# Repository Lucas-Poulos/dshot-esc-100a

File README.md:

# dshot-esc-100a

A 12 V, 100 A three-phase **all-N-channel** motor driver for a high-power
drone motor, controllable over **DShot150/300/600/1200**.

| | |
|---|---|
| Battery | 3S LiPo, 9.0–12.6 V (operating range 6–16 V) |
| Continuous | **100 A** (~1.2 kW) |
| Burst | **150 A** for 10 s |
| Bridge | 6 switch positions × **2 paralleled N-channel MOSFETs = 12 total** |
| Gate driver | **DRV8323R** (RS or RH — one footprint, both variants) |
| Controller | **STM32G071CBT6** running **AM32** |
| Control | DShot150/300/600/1200, bidirectional, + ESC telemetry |
| Efficiency | ~98.5 % at 100 A (≈19 W dissipated) |

**Status: schematic complete and ERC-clean (160 components). PCB floorplanned
and DRC-clean — 80 × 68 mm, 4 layers, 2 oz outer. Routing not started.**

---

## Why all N-channel, and how the high side is driven

A P-channel high-side switch is the easy way to build a bridge and the
wrong way here — P-channel parts with usable R_DS(on) at 100 A don't exist
in a sane package. Both rails are N-channel, so the high-side gate has to
be driven above the battery rail.

The DRV8323R does that with an on-chip **charge pump**, not a bootstrap
capacitor. A bootstrap cap must be refreshed by pulling the phase node
low, which caps duty cycle below 100 %. A charge pump holds the gate up
indefinitely, so the high-side FET stays fully enhanced at **100 % duty** —
exactly the regime "drive it hard" lives in.

## Shoot-through: four independent layers

Shoot-through at 12 V into 2 × 0.43 mΩ is roughly **14 kA**, limited only
by parasitics. It destroys the bridge in microseconds and no fuse is fast
enough. So it's prevented four times over, and no single layer is trusted:

| Layer | Mechanism | Independent of |
|---|---|---|
| 1 | TIM1 hardware dead-time generator, **625 ns** | firmware timing bugs |
| 2 | DRV8323R cross-conduction lockout + 100 ns | the MCU entirely |
| 3 | 6 × SN74LVC1G97 combinational interlock | MCU *and* driver |
| 4 | Gate-source pulldowns + per-FET series gate resistors | everything active |
| 0 | `nFAULT` → `TIM1_BKIN` kills all 6 outputs in hardware | firmware latency |

The dead-time budget works out **negative** under nominal conditions —
because sink current is set 3.5× source current, the outgoing FET is
already off before the incoming one conducts. The 625 ns is therefore pure
margin against V_th spread, tempco, and gate ringing. Full derivation from
the FET's measured gate charge: **[`docs/shoot-through.md`](docs/shoot-through.md)**.

## Documentation

| Document | What's in it |
|---|---|
| [`docs/architecture.md`](docs/architecture.md) | topology, block diagram, sheet map, design decisions |
| [`docs/shoot-through.md`](docs/shoot-through.md) | the four layers, dead-time budget, DTG encoding |
| [`docs/power-budget.md`](docs/power-budget.md) | conduction/switching/shunt losses, thermals, why 2 FETs not 3 |
| [`docs/pinout.md`](docs/pinout.md) | full 48-pin MCU map + AM32 hardware group |
| [`docs/gate-driver-config.md`](docs/gate-driver-config.md) | RH vs RS dual build, every register value derived |
| [`docs/layout.md`](docs/layout.md) | stackup, floorplan, and the routing rules — **read before routing** |
| [`docs/references.md`](docs/references.md) | every datasheet and firmware source used |
| [`firmware/README.md`](firmware/README.md) | AM32 target, SPI init, flashing, **bring-up order** |
| [`manufacturing/BOM.md`](manufacturing/BOM.md) | generated from the netlist, real LCSC numbers |
| [`manufacturing/dshot-esc-100a/ISSUES.md`](manufacturing/dshot-esc-100a/ISSUES.md) | 12 open items — read before fabricating |

## Repository layout

```
design/          GENERATED KiCad 10 project — schematic never saved from the GUI
  01_power_in  02_gate_driver  03_power_stage
  04_mcu       05_sense        06_protection
  lib/         DRV8323R + STM32G071CBTx symbols
scripts/        the source of truth for everything in design/
  gen_custom_symbols.py  gen_project.py  wire_sheets.py
  gen_footprints.py      gen_pcb.py      verify_project.py
  gen_bom.py             calc_*.py
  kicad_sch.py           kicad_symlib.py
docs/           design documentation
firmware/       AM32 target + DRV8323RS SPI driver
datasheets/     22 PDFs, synced from LCSC
manufacturing/  BOM, schematic PDF, issue tracker
```

## Reproducing the design

```bash
pgrep -fil kicad                            # must be empty first
python3 scripts/gen_custom_symbols.py       # symbol library
python3 scripts/gen_project.py --verify     # refuses to write if broken
python3 scripts/gen_project.py              # sheets + placement + wiring
python3 scripts/gen_bom.py
python3 scripts/verify_project.py           # the real gate
```

The calculations behind the docs are runnable, not asserted:

```bash
python3 scripts/calc_deadtime.py    # DTG table + dead-time budget
python3 scripts/calc_power.py       # loss and thermal budget
```

## Before you build one

Read [`ISSUES.md`](manufacturing/dshot-esc-100a/ISSUES.md). 11 open, 2
resolved. The ones that still matter most:

- **ESC-001** — the input ripple budget (~50 A RMS) isn't closed.
- **ESC-005** — the shunt needs a Kelvin sense tap in layout; at 0.25 mΩ
  a few mΩ of shared trace is a large error.
- **ESC-012** — 19 W is **not** passively coolable; this design assumes
  forced air.
- **ESC-007** — the buck feedback divider is unverified. Check it before
  first power-on or the MCU may sit outside its supply range.

And follow the bring-up order in `firmware/README.md`. Do not put a motor
on this board first.

## Licence

Hardware: CERN-OHL-S v2. Firmware snippets: MIT, matching AM32.

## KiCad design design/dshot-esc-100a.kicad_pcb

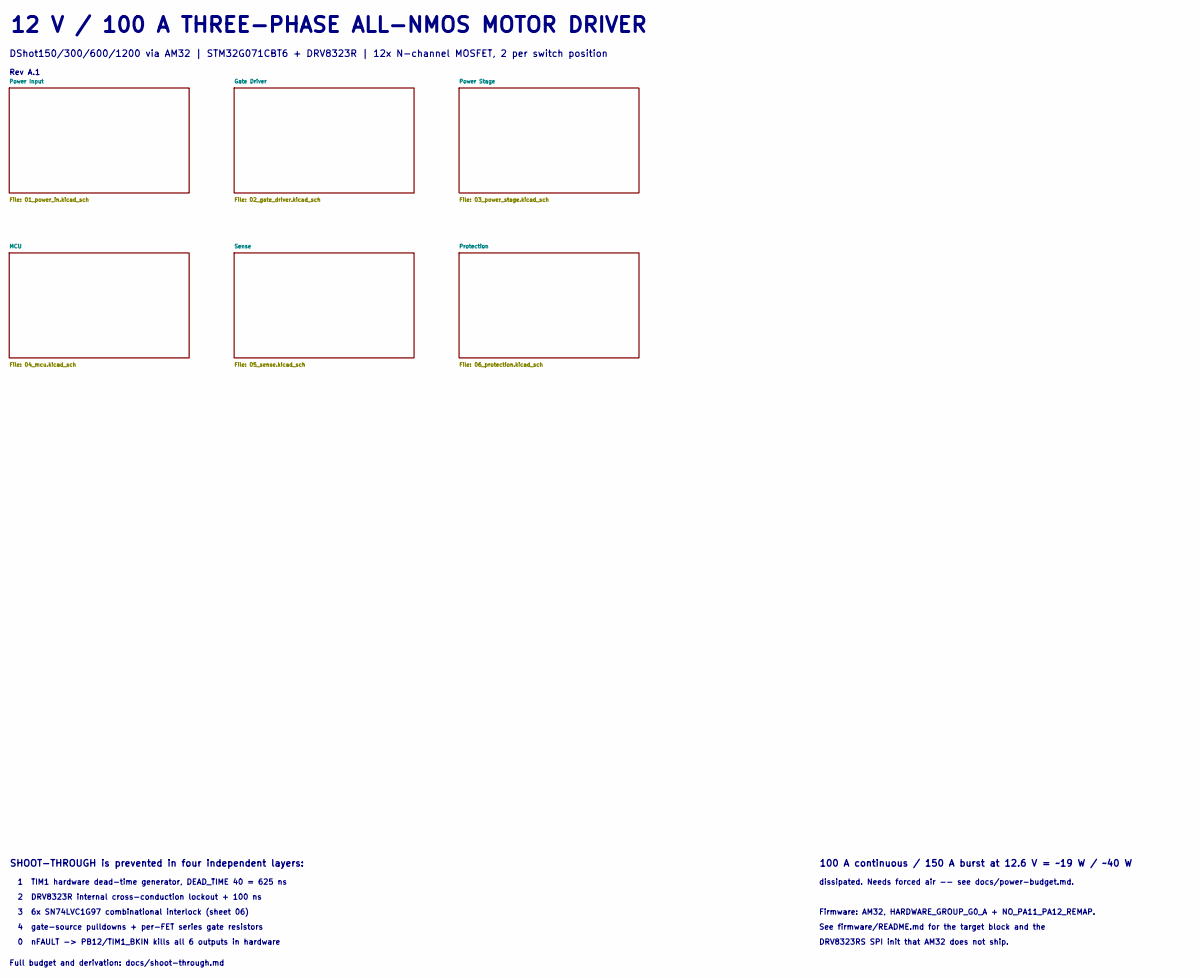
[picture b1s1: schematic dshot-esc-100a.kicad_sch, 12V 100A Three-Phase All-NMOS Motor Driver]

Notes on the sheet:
2 DRV8323R internal cross-conduction lockout + 100 ns
Full budget and derivation: docs/shoot-through.md
dissipated. Needs forced air -- see docs/power-budget.md.
12 V / 100 A THREE-PHASE ALL-NMOS MOTOR DRIVER
Rev A.1
See firmware/README.md for the target block and the
DRV8323RS SPI init that AM32 does not ship.
4 gate-source pulldowns + per-FET series gate resistors
SHOOT-THROUGH is prevented in four independent layers:
1 TIM1 hardware dead-time generator, DEAD_TIME 40 = 625 ns
Firmware: AM32, HARDWARE_GROUP_G0_A + NO_PA11_PA12_REMAP.
DShot150/300/600/1200 via AM32 | STM32G071CBT6 + DRV8323R | 12x N-channel MOSFET, 2 per switch position
0 nFAULT -> PB12/TIM1_BKIN kills all 6 outputs in hardware
3 6x SN74LVC1G97 combinational interlock (sheet 06)
100 A continuous / 150 A burst at 12.6 V = ~19 W / ~40 W

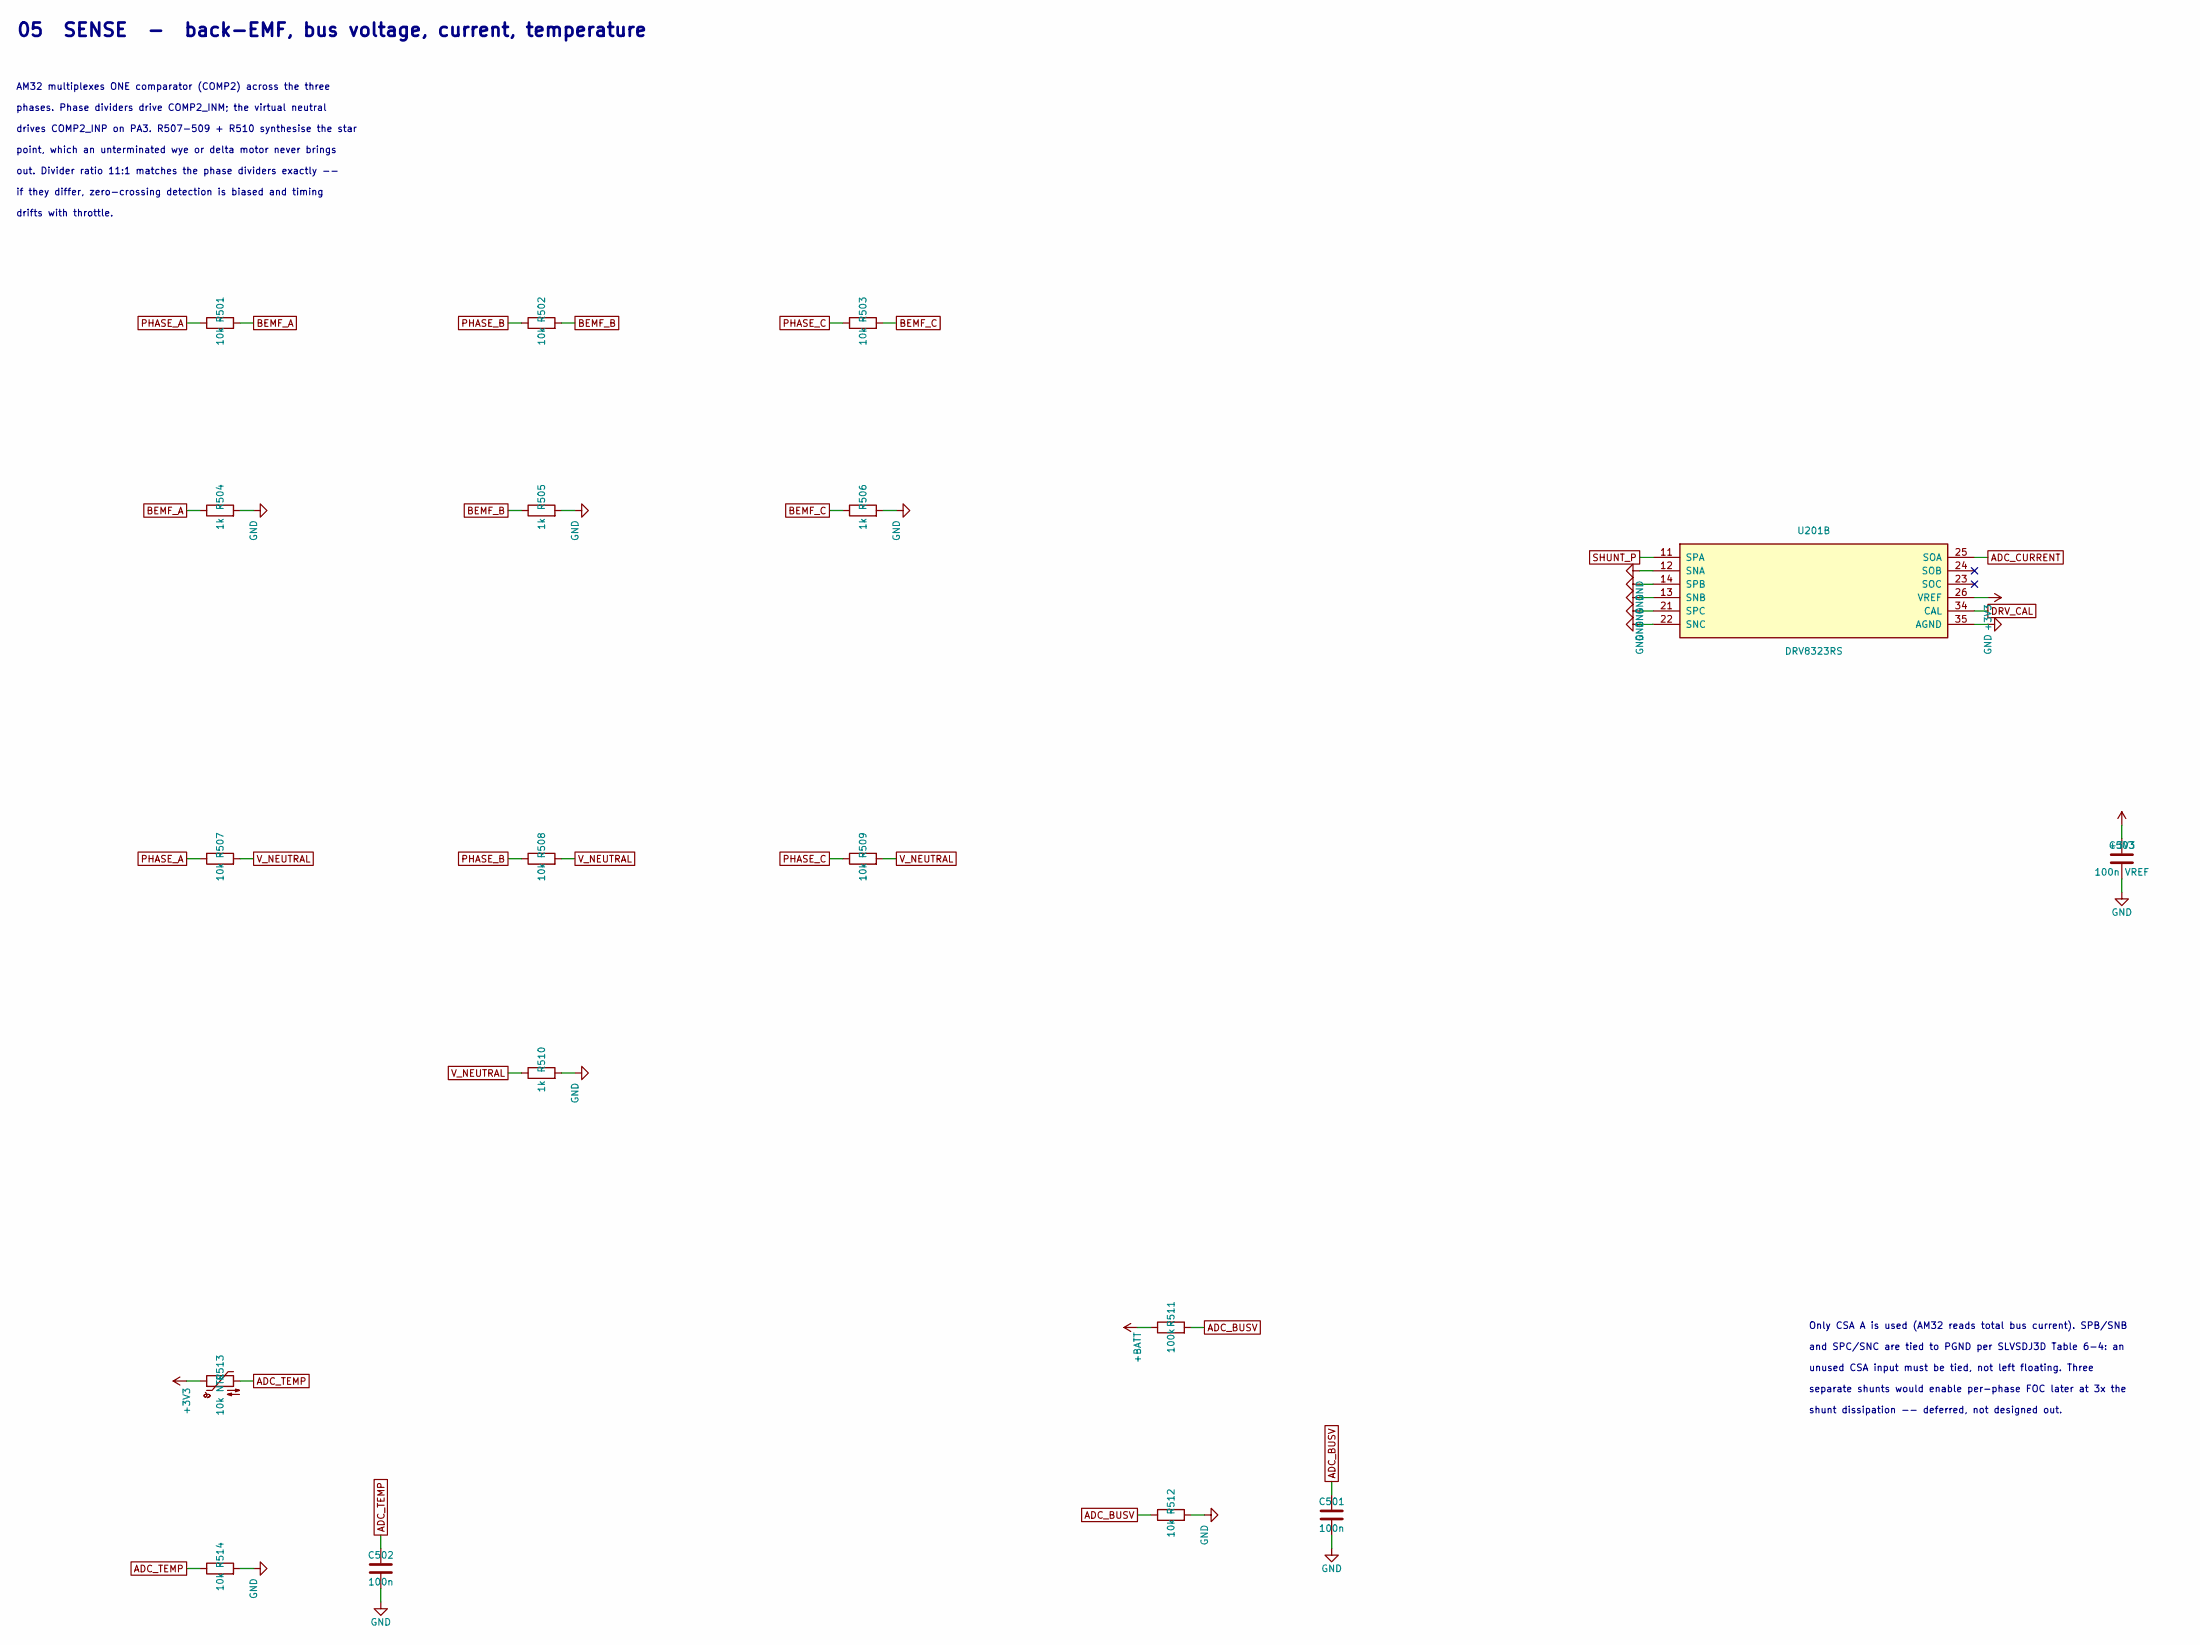
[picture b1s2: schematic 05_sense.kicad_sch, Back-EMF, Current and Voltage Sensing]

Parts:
C501, C502: 100n; C_0603_1608Metric; MPN CC0603KRX7R9BB104; LCSC C14663
C503: 100n VREF; C_0603_1608Metric; MPN CC0603KRX7R9BB104; LCSC C14663
R501, R502, R503, R507, R508, R509, R512, R514: 10k; R_0603_1608Metric; MPN FRC0603F1002TS; LCSC C2906982
R504, R505, R506, R510: 1k; R_0603_1608Metric; MPN FRC0603F1001TS; LCSC C2907002
R511: 100k; R_0603_1608Metric; MPN 0603WAF1003T5E; LCSC C25803
R513: 10k NTC; R_0603_1608Metric; MPN NCP18XH103F03RB; LCSC C13564
U201: DRV8323RS; Texas_RGZ0048A_VQFN-48-1EP_7x7mm_P0.5mm_EP5.15x5.15mm; MPN DRV8323RSRGZT; LCSC C2653553

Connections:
+3V3: C503.1, R513.1, U201.26 (VREF); also elsewhere on the board
+BATT: R511.1; also elsewhere on the board
ADC_BUSV: C501.1, R511.2, R512.1; also elsewhere on the board
ADC_CURRENT: U201.25 (SOA); also elsewhere on the board
ADC_TEMP: C502.1, R513.2, R514.1; also elsewhere on the board
BEMF_A: R501.2, R504.1; also elsewhere on the board
BEMF_B: R502.2, R505.1; also elsewhere on the board
BEMF_C: R503.2, R506.1; also elsewhere on the board
DRV_CAL: U201.34 (CAL); also elsewhere on the board
GND: C501.2, C502.2, C503.2, R504.2, R505.2, R506.2, R510.2, R512.2, R514.2, U201.12 (SNA), U201.13 (SNB), U201.14 (SPB), U201.21 (SPC), U201.22 (SNC), U201.35 (AGND); also elsewhere on the board
PHASE_A: R501.1, R507.1; also elsewhere on the board
PHASE_B: R502.1, R508.1; also elsewhere on the board
PHASE_C: R503.1, R509.1; also elsewhere on the board
SHUNT_P: U201.11 (SPA); also elsewhere on the board
V_NEUTRAL: R507.2, R508.2, R509.2, R510.1; also elsewhere on the board

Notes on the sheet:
point, which an unterminated wye or delta motor never brings
out. Divider ratio 11:1 matches the phase dividers exactly --
shunt dissipation -- deferred, not designed out.
05 SENSE - back-EMF, bus voltage, current, temperature
drives COMP2_INP on PA3. R507-509 + R510 synthesise the star
drifts with throttle.
unused CSA input must be tied, not left floating. Three
AM32 multiplexes ONE comparator (COMP2) across the three
phases. Phase dividers drive COMP2_INM; the virtual neutral
if they differ, zero-crossing detection is biased and timing
separate shunts would enable per-phase FOC later at 3x the
and SPC/SNC are tied to PGND per SLVSDJ3D Table 6-4: an
Only CSA A is used (AM32 reads total bus current). SPB/SNB

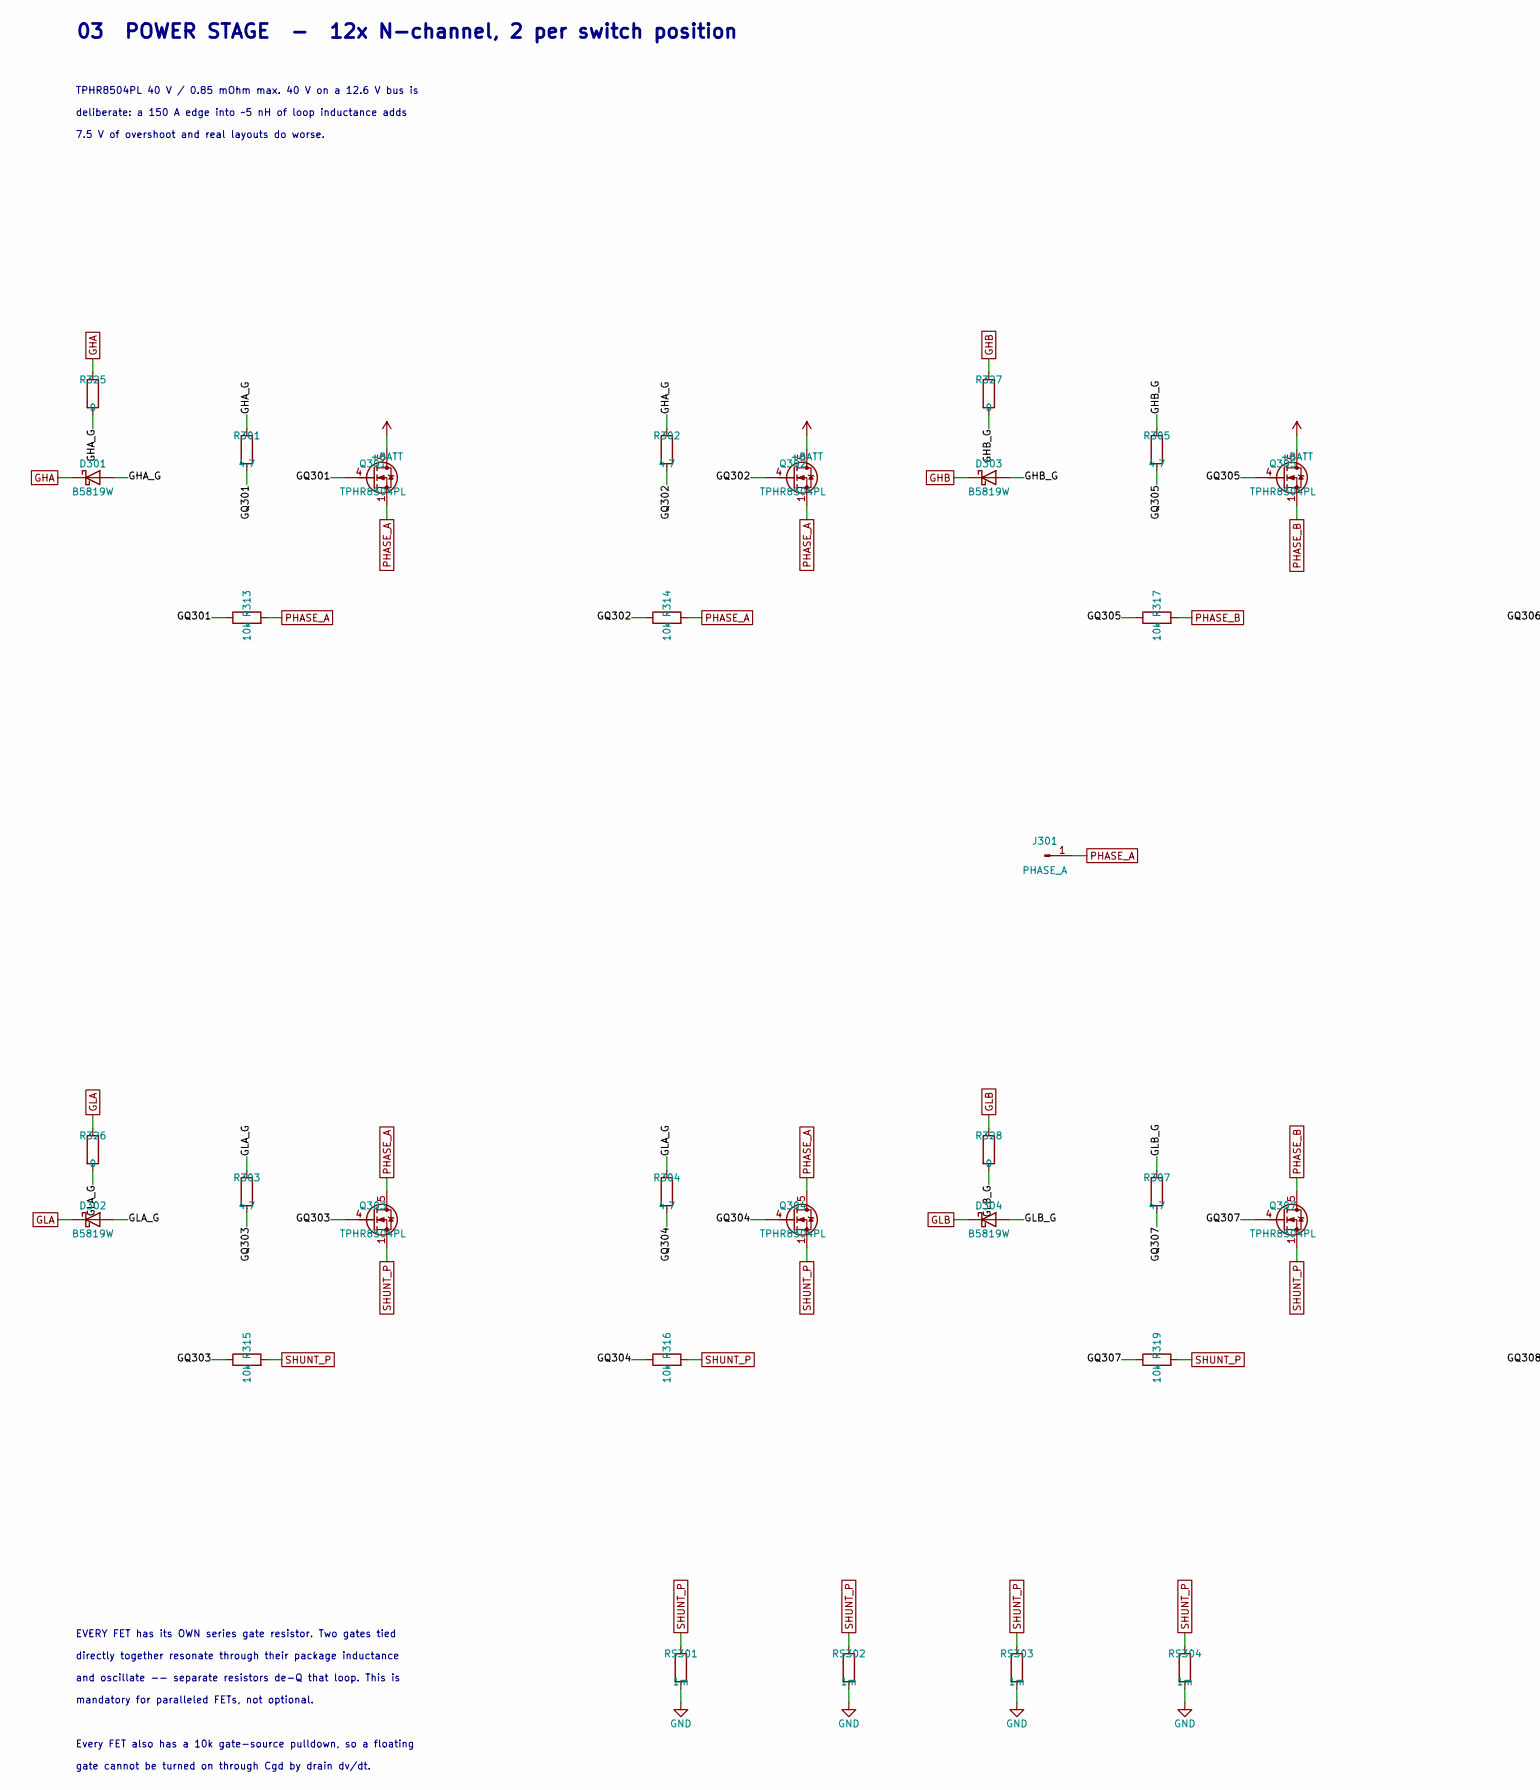
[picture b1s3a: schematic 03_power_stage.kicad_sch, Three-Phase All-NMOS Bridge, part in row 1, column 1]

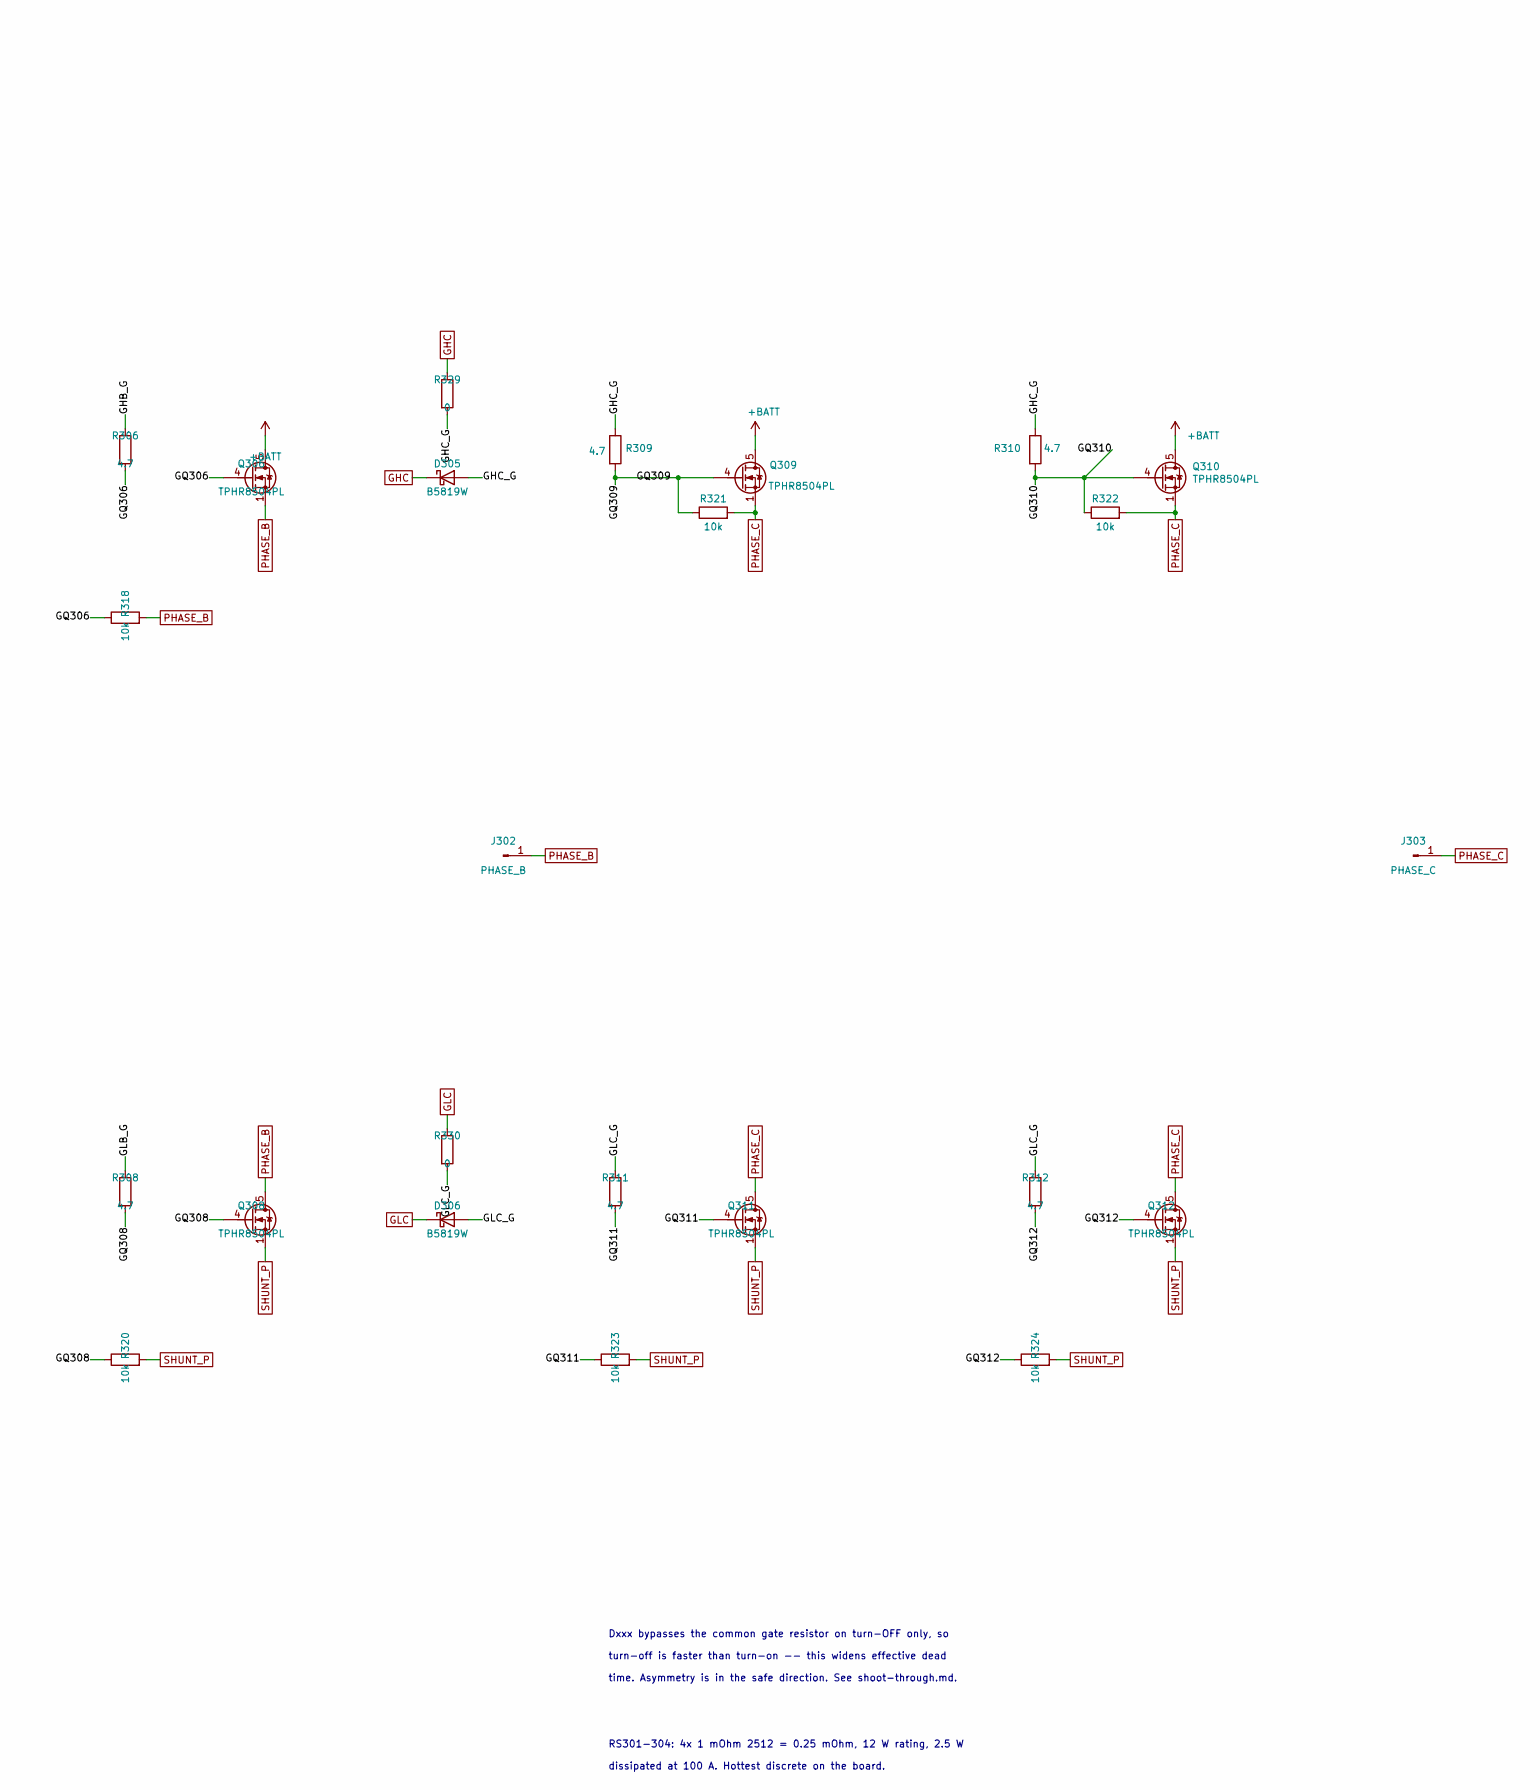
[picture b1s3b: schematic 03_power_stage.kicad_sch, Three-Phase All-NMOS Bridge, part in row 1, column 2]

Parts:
D301, D302, D303, D304, D305, D306: B5819W; D_SOD-123; MPN B5819W SL; LCSC C8598
J301: PHASE_A; HighCurrentTerminal_8AWG
J302: PHASE_B; HighCurrentTerminal_8AWG
J303: PHASE_C; HighCurrentTerminal_8AWG
Q301, Q302, Q303, Q304, Q305, Q306, Q307, Q308, Q309, Q310, Q311, Q312: TPHR8504PL; PQFN-8-EP_6x5mm_P1.27mm_Generic; MPN TPHR8504PL,L1Q(M; LCSC C5331611
R301, R302, R303, R304, R305, R306, R307, R308, R309, R310, R311, R312: 4.7; R_0805_2012Metric; MPN FRC0805F4R70TS; LCSC C2933459
R313, R314, R315, R316, R317, R318, R319, R320, R321, R322, R323, R324: 10k; R_0603_1608Metric; MPN FRC0603F1002TS; LCSC C2906982
R325, R326, R327, R328, R329, R330: 0; R_0603_1608Metric; MPN RCA030RLF; LCSC C22356631
RS301, RS302, RS303, RS304: 1m; R_2512_6332Metric; MPN HoJLR2512-3W-1mR-1%; LCSC C2903470

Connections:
+BATT: Q301.5 (D), Q302.5 (D), Q305.5 (D), Q306.5 (D), Q309.5 (D), Q310.5 (D); also elsewhere on the board
/Power Stage/GHA_G: D301.2 (A), R301.1, R302.1, R325.2
/Power Stage/GHB_G: D303.2 (A), R305.1, R306.1, R327.2
/Power Stage/GHC_G: D305.2 (A), R309.1, R310.1, R329.2
/Power Stage/GLA_G: D302.2 (A), R303.1, R304.1, R326.2
/Power Stage/GLB_G: D304.2 (A), R307.1, R308.1, R328.2
/Power Stage/GLC_G: D306.2 (A), R311.1, R312.1, R330.2
/Power Stage/GQ301: Q301.4 (G), R301.2, R313.1
/Power Stage/GQ302: Q302.4 (G), R302.2, R314.1
/Power Stage/GQ303: Q303.4 (G), R303.2, R315.1
/Power Stage/GQ304: Q304.4 (G), R304.2, R316.1
/Power Stage/GQ305: Q305.4 (G), R305.2, R317.1
/Power Stage/GQ306: Q306.4 (G), R306.2, R318.1
/Power Stage/GQ307: Q307.4 (G), R307.2, R319.1
/Power Stage/GQ308: Q308.4 (G), R308.2, R320.1
/Power Stage/GQ309: Q309.4 (G), R309.2, R321.1
/Power Stage/GQ310: Q310.4 (G), R310.2, R322.1
/Power Stage/GQ311: Q311.4 (G), R311.2, R323.1
/Power Stage/GQ312: Q312.4 (G), R312.2, R324.1
GHA: D301.1 (K), R325.1; also elsewhere on the board
GHB: D303.1 (K), R327.1; also elsewhere on the board
GHC: D305.1 (K), R329.1; also elsewhere on the board
GLA: D302.1 (K), R326.1; also elsewhere on the board
GLB: D304.1 (K), R328.1; also elsewhere on the board
GLC: D306.1 (K), R330.1; also elsewhere on the board
GND: RS301.2, RS302.2, RS303.2, RS304.2; also elsewhere on the board
PHASE_A: J301.1, Q301.1 (S), Q301.2 (S), Q301.3 (S), Q302.1 (S), Q302.2 (S), Q302.3 (S), Q303.5 (D), Q304.5 (D), R313.2, R314.2; also elsewhere on the board
PHASE_B: J302.1, Q305.1 (S), Q305.2 (S), Q305.3 (S), Q306.1 (S), Q306.2 (S), Q306.3 (S), Q307.5 (D), Q308.5 (D), R317.2, R318.2; also elsewhere on the board
PHASE_C: J303.1, Q309.1 (S), Q309.2 (S), Q309.3 (S), Q310.1 (S), Q310.2 (S), Q310.3 (S), Q311.5 (D), Q312.5 (D), R321.2, R322.2; also elsewhere on the board
SHUNT_P: Q303.1 (S), Q303.2 (S), Q303.3 (S), Q304.1 (S), Q304.2 (S), Q304.3 (S), Q307.1 (S), Q307.2 (S), Q307.3 (S), Q308.1 (S), Q308.2 (S), Q308.3 (S), Q311.1 (S), Q311.2 (S), Q311.3 (S), Q312.1 (S), Q312.2 (S), Q312.3 (S), R315.2, R316.2, R319.2, R320.2, R323.2, R324.2, RS301.1, RS302.1, RS303.1, RS304.1; also elsewhere on the board

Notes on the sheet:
and oscillate -- separate resistors de-Q that loop. This is
time. Asymmetry is in the safe direction. See shoot-through.md.
turn-off is faster than turn-on -- this widens effective dead
RS301-304: 4x 1 mOhm 2512 = 0.25 mOhm, 12 W rating, 2.5 W
TPHR8504PL 40 V / 0.85 mOhm max. 40 V on a 12.6 V bus is
directly together resonate through their package inductance
mandatory for paralleled FETs, not optional.
Every FET also has a 10k gate-source pulldown, so a floating
dissipated at 100 A. Hottest discrete on the board.
03 POWER STAGE - 12x N-channel, 2 per switch position
deliberate: a 150 A edge into ~5 nH of loop inductance adds
Dxxx bypasses the common gate resistor on turn-OFF only, so
EVERY FET has its OWN series gate resistor. Two gates tied
7.5 V of overshoot and real layouts do worse.
gate cannot be turned on through Cgd by drain dv/dt.

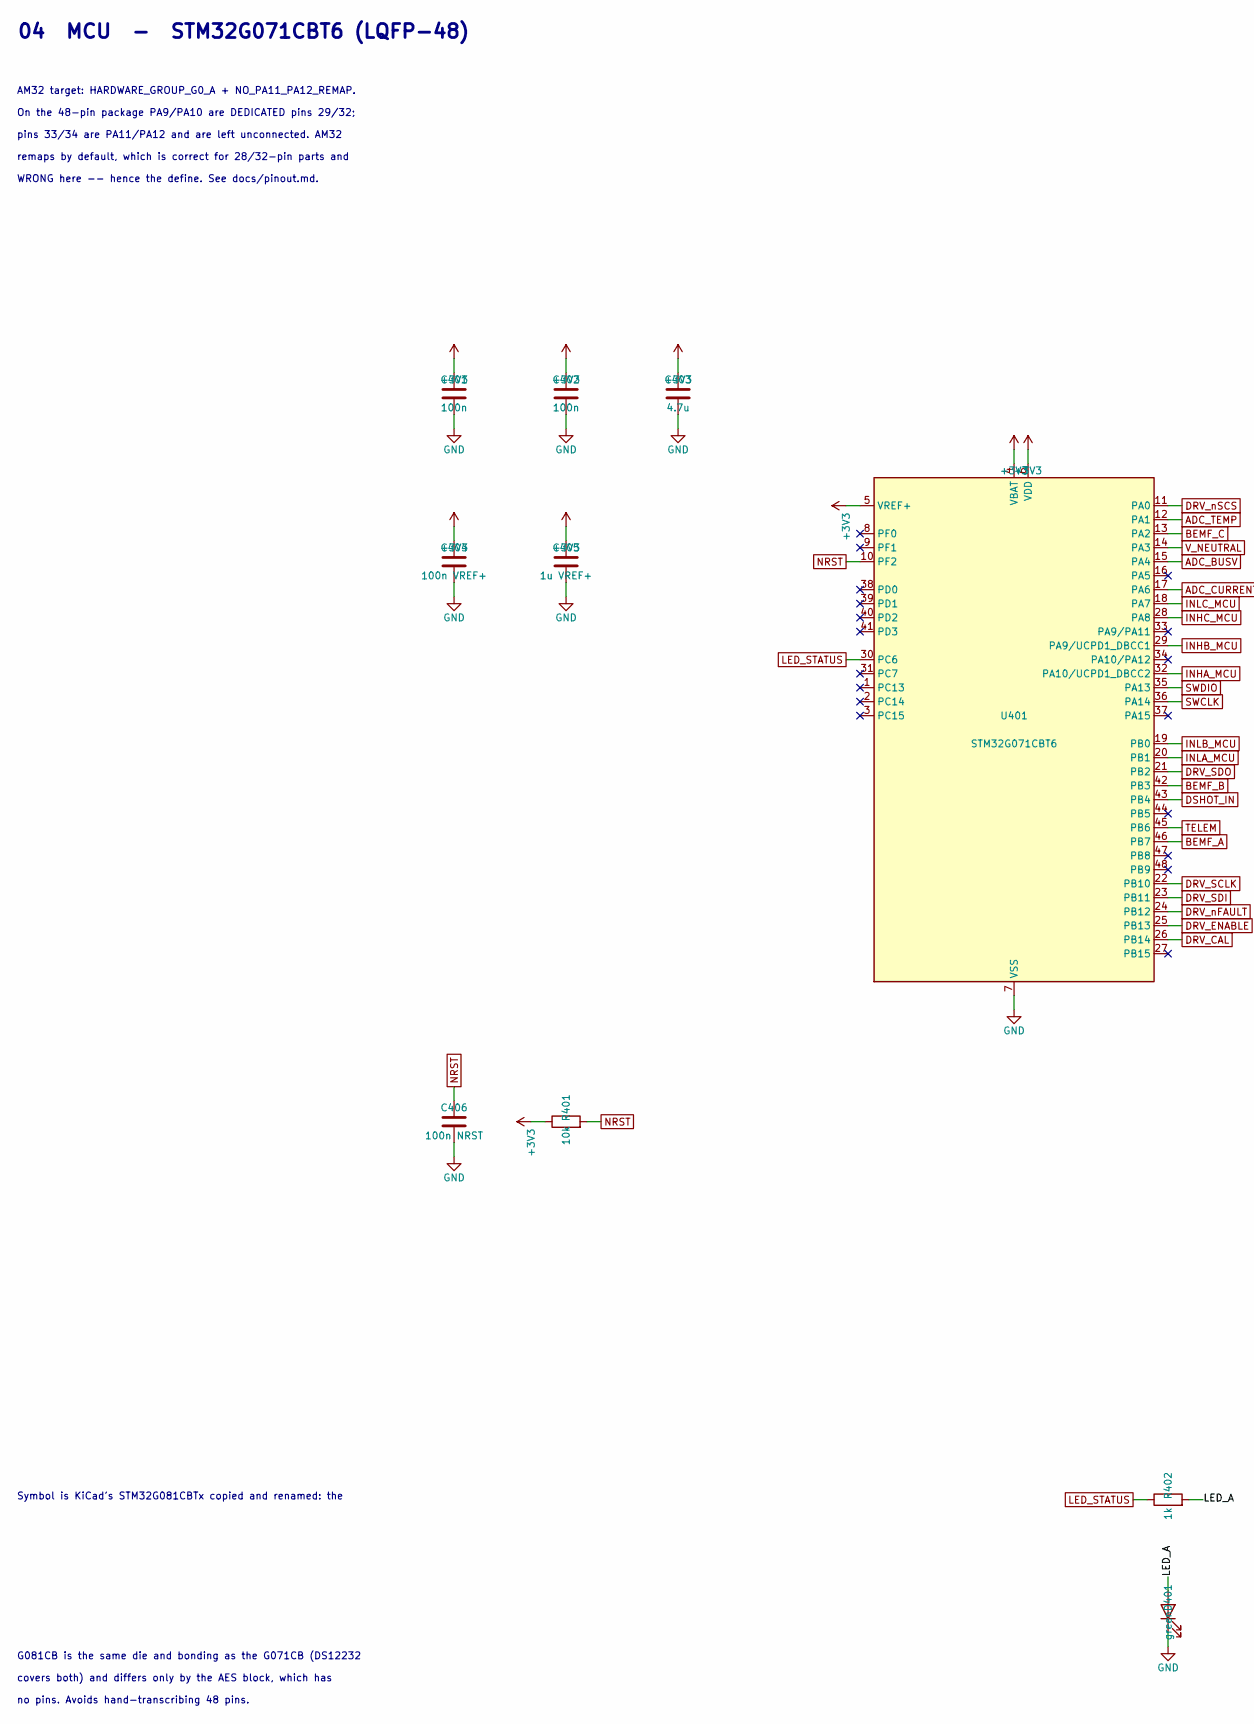
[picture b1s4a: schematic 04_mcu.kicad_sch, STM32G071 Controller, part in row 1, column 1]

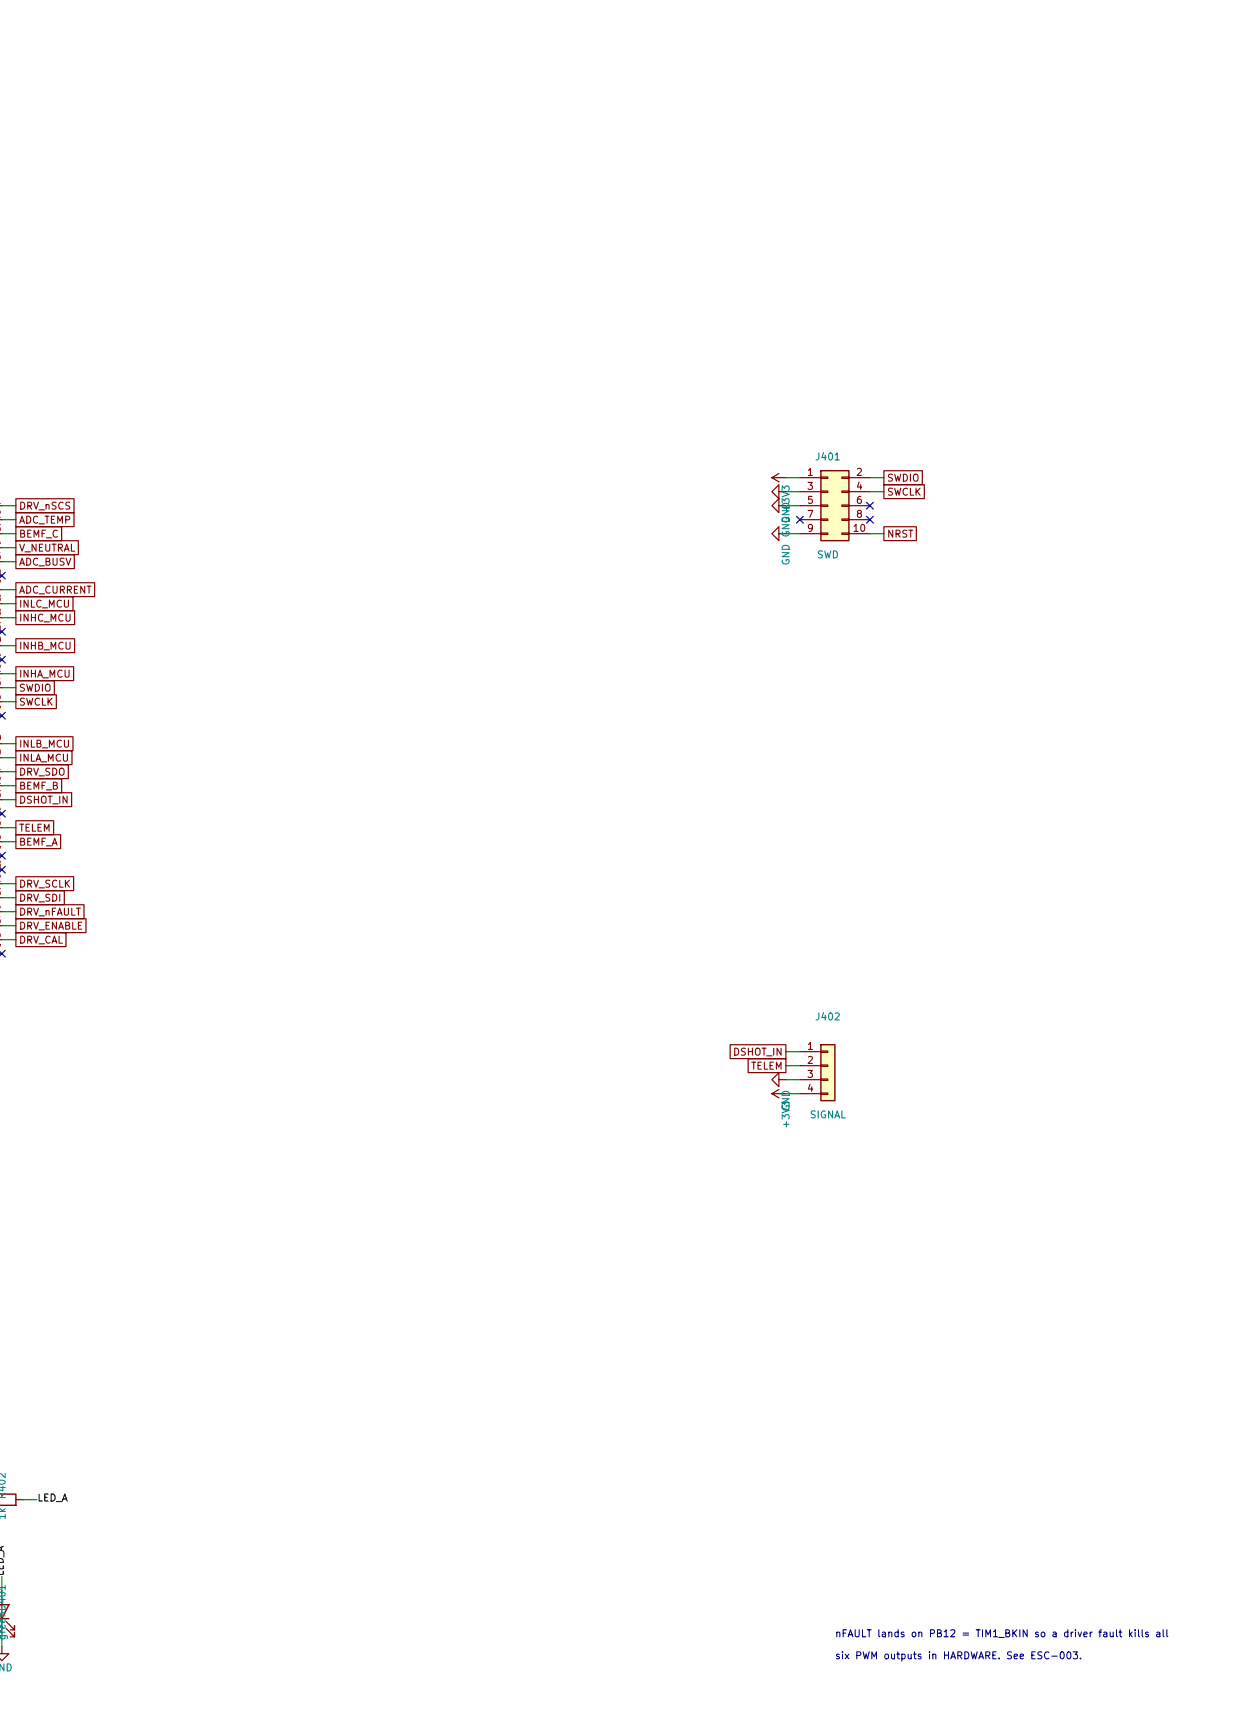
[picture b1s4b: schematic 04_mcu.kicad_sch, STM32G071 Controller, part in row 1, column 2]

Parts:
C401, C402: 100n; C_0603_1608Metric; MPN CC0603KRX7R9BB104; LCSC C14663
C403: 4.7u; C_0805_2012Metric; MPN CL21B475KAFNNNE; LCSC C98195
C404: 100n VREF+; C_0603_1608Metric; MPN CC0603KRX7R9BB104; LCSC C14663
C405: 1u VREF+; C_0603_1608Metric; MPN CL10B105KA8NNNC; LCSC C29936
C406: 100n NRST; C_0603_1608Metric; MPN CC0603KRX7R9BB104; LCSC C14663
D401: green; LED_0603_1608Metric; MPN XL-1608UGC-04; LCSC C965804
J401: SWD; PinHeader_2x05_P1.27mm_Vertical
J402: SIGNAL; PinHeader_1x04_P2.54mm_Vertical
R401: 10k; R_0603_1608Metric; MPN FRC0603F1002TS; LCSC C2906982
R402: 1k; R_0603_1608Metric; MPN FRC0603F1001TS; LCSC C2907002
U401: STM32G071CBT6; LQFP-48_7x7mm_P0.5mm; MPN STM32G071CBT6; LCSC C432212

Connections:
+3V3: C401.1, C402.1, C403.1, C404.1, C405.1, J401.1, J402.4, R401.1, U401.4 (VBAT), U401.5 (VREF+), U401.6 (VDD); also elsewhere on the board
/MCU/LED_A: D401.2 (A), R402.2
ADC_BUSV: U401.15 (PA4); also elsewhere on the board
ADC_CURRENT: U401.17 (PA6); also elsewhere on the board
ADC_TEMP: U401.12 (PA1); also elsewhere on the board
BEMF_A: U401.46 (PB7); also elsewhere on the board
BEMF_B: U401.42 (PB3); also elsewhere on the board
BEMF_C: U401.13 (PA2); also elsewhere on the board
DRV_CAL: U401.26 (PB14); also elsewhere on the board
DRV_ENABLE: U401.25 (PB13); also elsewhere on the board
DRV_SCLK: U401.22 (PB10); also elsewhere on the board
DRV_SDI: U401.23 (PB11); also elsewhere on the board
DRV_SDO: U401.21 (PB2); also elsewhere on the board
DRV_nFAULT: U401.24 (PB12); also elsewhere on the board
DRV_nSCS: U401.11 (PA0); also elsewhere on the board
DSHOT_IN: J402.1, U401.43 (PB4)
GND: C401.2, C402.2, C403.2, C404.2, C405.2, C406.2, D401.1 (K), J401.3, J401.5, J401.9, J402.3, U401.7 (VSS); also elsewhere on the board
INHA_MCU: U401.32 (PA10/UCPD1_DBCC2); also elsewhere on the board
INHB_MCU: U401.29 (PA9/UCPD1_DBCC1); also elsewhere on the board
INHC_MCU: U401.28 (PA8); also elsewhere on the board
INLA_MCU: U401.20 (PB1); also elsewhere on the board
INLB_MCU: U401.19 (PB0); also elsewhere on the board
INLC_MCU: U401.18 (PA7); also elsewhere on the board
LED_STATUS: R402.1, U401.30 (PC6)
NRST: C406.1, J401.10, R401.2, U401.10 (PF2)
SWCLK: J401.4, U401.36 (PA14)
SWDIO: J401.2, U401.35 (PA13)
TELEM: J402.2, U401.45 (PB6)
V_NEUTRAL: U401.14 (PA3); also elsewhere on the board

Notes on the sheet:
no pins. Avoids hand-transcribing 48 pins.
pins 33/34 are PA11/PA12 and are left unconnected. AM32
WRONG here -- hence the define. See docs/pinout.md.
04 MCU - STM32G071CBT6 (LQFP-48)
nFAULT lands on PB12 = TIM1_BKIN so a driver fault kills all
remaps by default, which is correct for 28/32-pin parts and
covers both) and differs only by the AES block, which has
G081CB is the same die and bonding as the G071CB (DS12232
six PWM outputs in HARDWARE. See ESC-003.
On the 48-pin package PA9/PA10 are DEDICATED pins 29/32;
AM32 target: HARDWARE_GROUP_G0_A + NO_PA11_PA12_REMAP.
Symbol is KiCad's STM32G081CBTx copied and renamed: the
